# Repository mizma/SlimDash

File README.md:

# SlimDash

ErgoDash inspired low-profile key switch keyboard with embedded RP2040

## Features

* Ortho-Staggered Split keyboard layout
* Slim body (20-22mm depending on key caps and rubber feet used)
* Rigid body structure
* Per-Key RGB LED Matrix lighting
* USB-C connector
* Easy build utilizing PCBA service
  * Hand Soldering needed:
    * 70 x Kailh choc v1 hotswap sockets
    * 4 x tactile switches (2 x BOOT is optional)
    * 2 x trrs jack
    * 70 SK6812MINI-E (optional for RGB matrix)
  * Assembly
    * Just PH001 Philips screws necessary

### Variations

Currently there is only one variation.

* SlimDash rev.1
  * See the [readme](./hardware-rev1/README.md) in the hardware-rev1
    directory for build instructions.
  * For firmware, see the release section for pre-built firmware,
    or see [here](./firmware/keyboards/mzmkb/slimdash/) for the build source.
    * To build from source, follow the [instructions](https://docs.qmk.fm/newbs_getting_started)
      and copy the keyboard sources from this repo (until the keyboard
      is merged upstream) to build.

## Acknowlegements

* [ErgoDash by omkbd](https://github.com/omkbd/ErgoDash)
  * Inspiration for this keyboard
* [ergogen](https://github.com/ergogen/ergogen)
  * Tooling to assist in the key layout and mechanical design
* Tutorials to get me started with ergogen
  * [Let's Design A Keyboard With Ergogen v4](https://flatfootfox.com/ergogen-part2-outlines/)
  * [I Built My Dream Keyboard from Absolute Scratch](https://www.youtube.com/watch?v=7UXsD7nSfDY)
* Tools used for making `keyboard.json` _less_ tedious.
  * [KLE](https://www.keyboard-layout-editor.com/)
  * [Keyboard Firmware Builder](https://kbfirmware.com/)
  * [KBFirmware to qmk converter](https://noroadsleft.github.io/kbf_qmk_converter/)

## License

[SlimDash](https://github.com/mizma/SlimDash) by
[mizma](https://github.com/mizma) is licensed under
[Creative Commons Attribution-ShareAlike 4.0 International](https://creativecommons.org/licenses/by-sa/4.0/?ref=chooser-v1)
 -
 -

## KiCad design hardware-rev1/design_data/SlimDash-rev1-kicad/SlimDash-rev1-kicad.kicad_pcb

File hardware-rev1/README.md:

# hardware-rev1 Build Instructions

__IMPORTANT__.  Read through the entire instruction first before starting
the Assembly so you have a good idea on what to expect!

日本語の手順は[こちら](./README_ja.md)

## Parts List (for one keyboard)

* PCB
  * Order with PCBA using ./hardware-rev1/PCB/slimdash_v1.0.0.zip and
    BOM/CPL files in the same directory.
  * You will need 2 PCBs for one set of keyboard
  * Ordering Instructions below.
* Acrylic: Order cuts for following (number required for one keyboard)
  * `backplate_1left_3mm-157.1x131.2.zip` x 1
  * `backplate_1right_3mm-155.2x131.2.zip` x 1
  * `backplate_2both_2mm-157.1x131.2.zip` x 1
  * `backplate_2left_2mm-157.1x131.2.zip` x 1
  * `backplate_3both_2mm-157.1x39.02.zip` x 2
  * `baseplate_left_2mm-155.2x131.2.zip` x 1
  * `baseplate_right_2mm-155.2x131.2.zip` x 1
  * `coverplate_both_2mm-20.05x81.60.zip` x 2
  * Ordering Instructions below.
* Screws/standoff
  * 14x m2x4 through-hole standoff x 7 x 2 = 14
    * <https://www.monotaro.com/p/1111/2876/>
  * 6x m2x10 through-hole standoff x 3 x 2 = 6
    * <https://www.monotaro.com/p/1111/2998/>
  * 32x m2x4 screws x (10 + 6) x 2 = 32
    * <https://www.monotaro.com/p/2902/9395/>
  * 8x m2x6 screws x 4 x 2 = 8
    * <https://www.monotaro.com/p/2902/9413/>
* Hand-Soldered Items
  * 70x Kailh low profile (choc v1) switches of your choice
  * 70x Kailh low profile hotswap sockets
    * Can be ordered from LCSC with part number [C5333465](https://www.lcsc.com/product-detail/Mechanical-Keyboard-Shaft_Kailh-CPG135001S30_C5333465.html)
  * 4x 3x6x4.3 horizontal tact switch
    * <https://shop.yushakobo.jp/collections/all-keyboard-parts/products/a1600ed-01-1>
    * You can also order from LCSC with part number [C18078123](https://www.lcsc.com/product-detail/Tactile-Switches_Bossie-BX-TS-26-3643ZJ_C18078123.html)
    * MJTP1117/PHAP3363 from DigiKey should work as well [679-2400-ND](https://www.digikey.com/en/products/detail/apem-inc/MJTP1117/1795496)
    * [schematics](images/tactile-switch_3x6x4.3.jpg)
  * 2x TRRS socket (MJ-4PP-9) connector
    * <https://shop.yushakobo.jp/products/a0800tr-01-1>
  * (optional) 70x SK6812MINI-E
    * <https://shop.yushakobo.jp/products/sk6812mini-e-10?variant=40047782953121>
    * [C5149201](https://www.lcsc.com/product-detail/RGB-LEDs-Built-in-IC_OPSCO-Optoelectronics-SK6812MINI-E_C5149201.html)
* A Kailh Choc v1 compatible keycap set
  * recommend ortho linear keycap set (some examples below)
  * [MBK Legend Glow R2](https://fkcaps.com/keycaps/mbk/legend-glow)
  * [Chosfox CFX](https://chosfox.com/collections/keycaps)
* Other Accessories
  * 1x TRRS Cable (Straight)
    * <https://shop.yushakobo.jp/products/self-made-cable?variant=39623339737249>
    * Anything with Tip-Ring-Ring-Sleeve type 2.5mm jack with straight wiring
      should work.
  * 1x USB-C Cable (Type-A to C or Type-C to C depending on your host PC connector)
  * 8x Rubber feet stickers

### PCB Ordering Instructions (JLCPCB)

1. Go to [JLCPCB](https://jlcpcb.com/jp/)
2. In the "Upload Gerber File" select the `./PCB/slimdash_v1.0.0.zip` file.
3. In the order settings, select the following options.
    * Base Material: FR-4
    * Layers: 2
    * Dimensions: Automatically filled in. __DON'T TOUCH__
    * PCB order volume: your choice
    * Product type: Industrial/Consumer Electronics
    * Alternate Designs: 1
    * Panilization: No Panilization
    * PCB Thickness: 1.6mm
    * PCB Color: your choice
    * Silkscreen: your choice
    * Surface Finish: your choice (HASL is fine)
    * Copper Thickness: 1 oz
    * Via: Resist Cover
    * Minimum via diameter: Keep default
    * PCB dimension tolerance: Keep default
    * Check Manufacturing data: your choice
    * PCB marking: remove marking
    * Electrical Test: Keep default
    * Card Edge connector: No
    * Castelated through-hole: No
    * Edge Plating: No
4. Select PCB Assembly option
    * PCBA Type: Economic
    * Assembly side: Top side
    * PCBA volume: same as PCB order volume (unless you are going to
      hand-solder SMT packages)
    * Tooling Hole: Added by Customer
    * Part Placement check: Yes
    * Part Selection: By Customer
    * Other Detail options: your choice.  Read JLCPCB descriptions carefully.
5. Go to next and Upload the [BOM](./PCB/bom.csv) file and [CPL](./PCB/CPL.csv) file
6. Check that the layout of the PCB has no errors. (It should look like the following)
    * 
7. Go to Quote and Order.

### Acrylic Ordering Instructions

1. Go to [Elecrow](https://www.elecrow.com/acrylic-cutting.html)
2. Upload each zip files in the Acrylic folder to order
    * Dimensions and Thickness should match the dimensions in the .zip file name.
      * i.e. for backplate_1left_3mm-157.1x131.2.zip, width x heigh should be 157.1x131.2
        and thickness of 3mm
    * Qty can be any number you require.
    * Color can be anything, but 2mm thickness only support Transparent, black or white.

## Assembly Instructions

First, solder the 90 degree tactile switch to the RST and BOOT.

The switch should be implemented on the top side for each hand.
Picture above shows the left hand side implementation.

Tact switch should be soldered before the TRRS jack.  TRRS jack
is then soldered on the same side of the board as the tactile
switches.

Once both the Tactile switches and the TRRS jack is implemented,
it should look like the following for left and right hand side.

After the TRRS and Tactile switches, apply pre-solder to one side of
the pad of each choc v1 hotswap sockets as shown below.

This pre-solder must be done on the opposite side from the tactile switches and
TRRS jacks.

After pre-solder is applied, place the hotswap sockets in place, and
use the soldering iron to pre-fuse the socket onto the pad.

Once the sockets are held in place, apply solder to the other side for
proper soldering, and then apply extra solder on the pre-fused side to
secure the socket in place.

When applying solder to the socket, make sure you do not over-apply solder.
If the solder bulges beyond the pad area (surpassing the yellow line in Picture
below), the acrylic will interfere and will not assemble properly.

If the solder interferes with the acrylic, don't force the assembly and remove
some solder using solder wick.

__OPTIONAL__: you may solder the SK6812MINI-E RGB LEDs at this point if you would
like.  See section below for extra instructions.

After Sockets are soldered, place the baseplate on the front side and insert
the kailh choc v1 keyswitches of your choice.  After all the switches are inserted,
place the 4mm long M2 spacer (standoff) from the back side, and loosely secure it
with the 4mm long M2 screws.

Flip the board to the back, place the backplate 1 ~ 3 and screw in the
4mm and 6mm screws. 6mm screws are used for the screw holes that go
through backplate 3.

After backplate is assembled, place the 10mm M2 spacer in the MCU areas
3 holes, and secure them with M2 screws, placing the coverplate on the top.
Put your choice of key caps.

You may apply rubber feet stickers on the back side for better stability and
stop the keyboard from sliding around in use.

### RGB Instructions

You will need to first jump the `JP1` solder jumper right next to the TRRS Jack.

Then solder the SK6812MINI-E from the back of the PCB, with the light emitting
side facing up.

See the pictures for the correct orientation (PIN1 is marked with yellow dot).

Note: the pin that has a diagonal cut is NOT PIN1.  Diagonal cut pin is diagonally
opposite from PIN1 marked on the picture above with yellow dot.

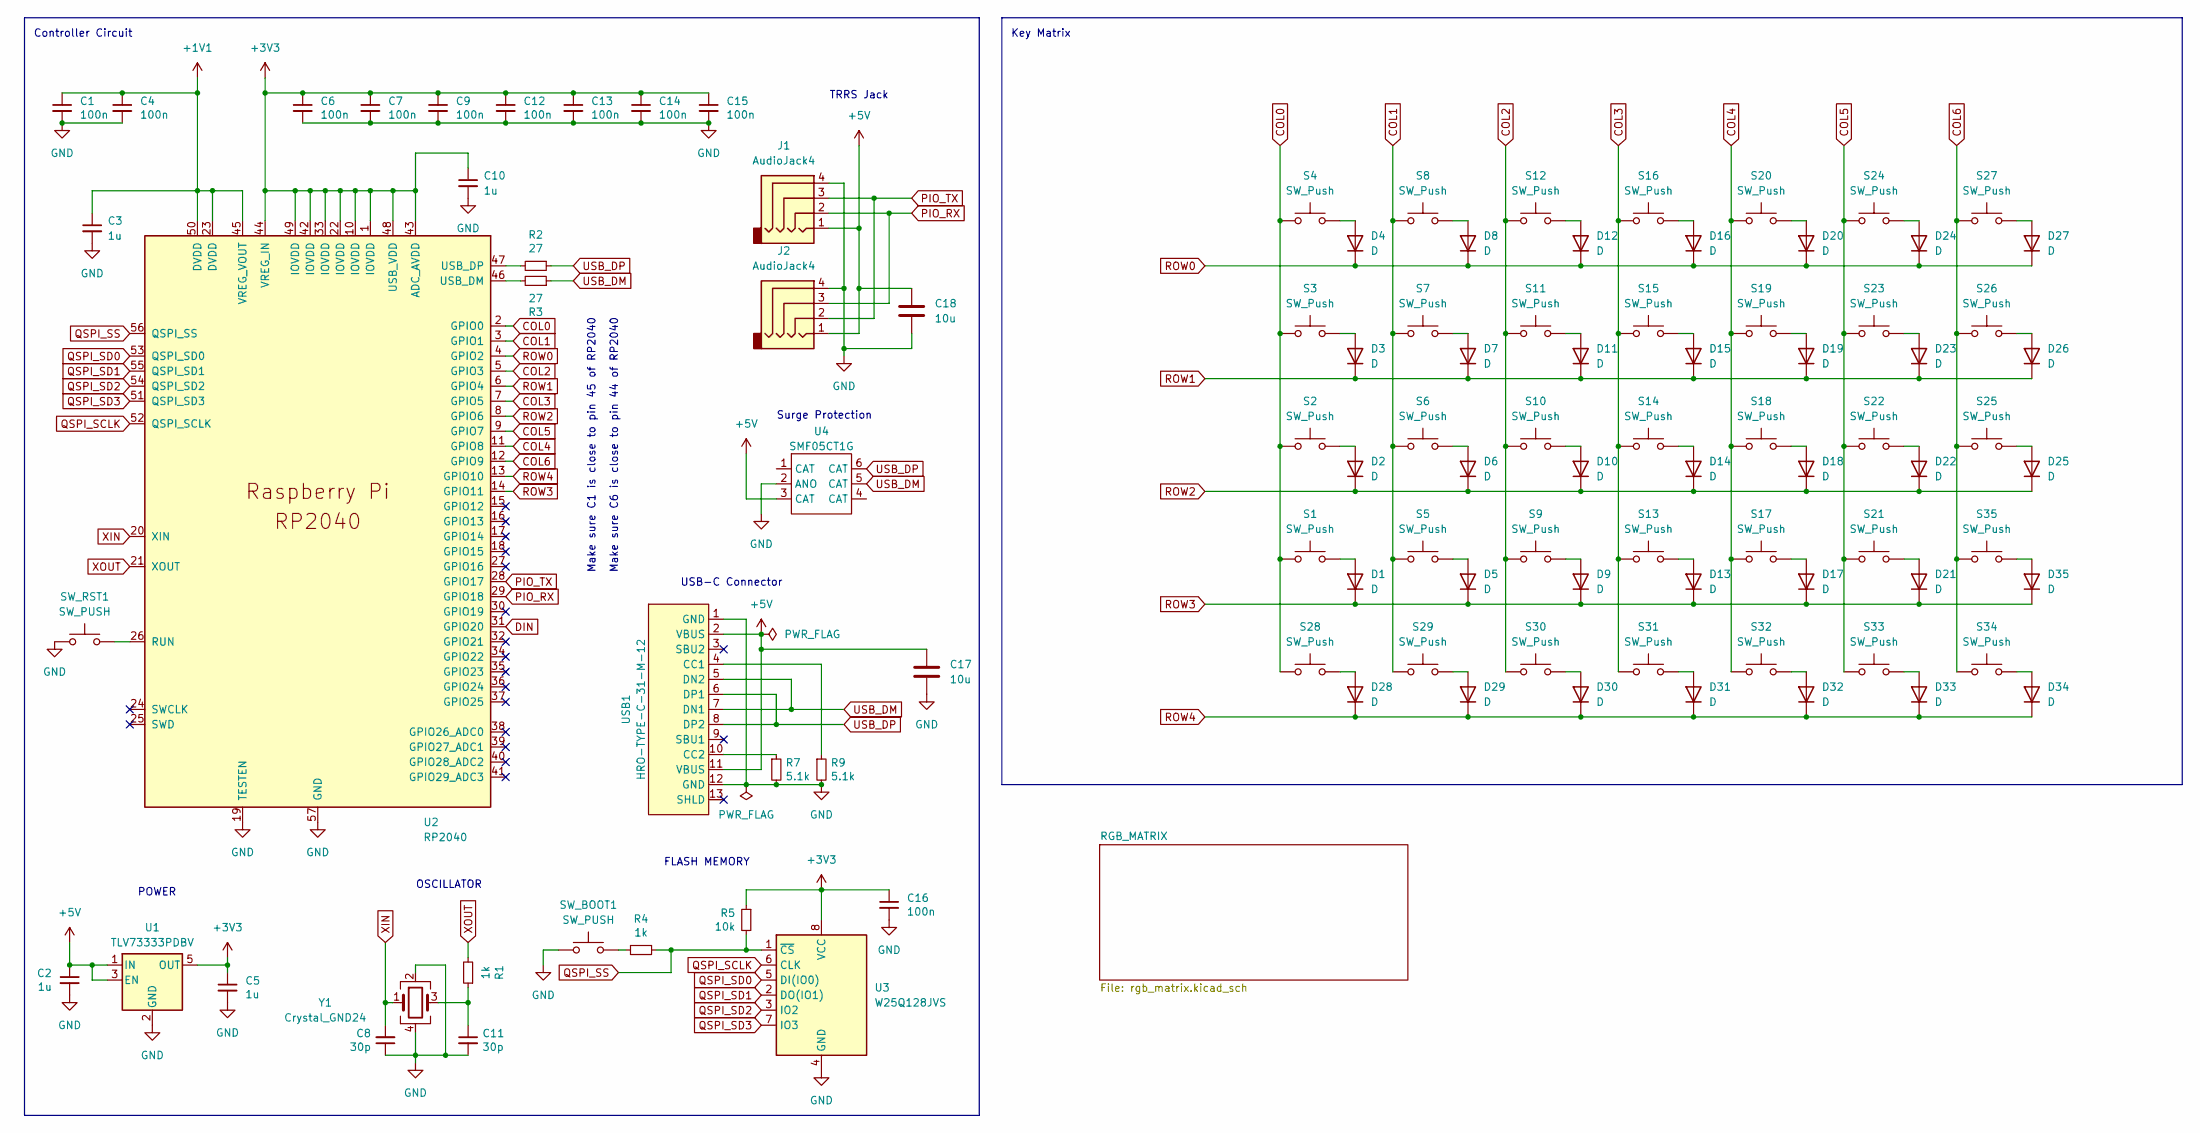
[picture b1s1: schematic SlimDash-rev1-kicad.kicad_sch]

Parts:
C1, C4, C6, C7, C9, C12, C13, C14, C15, C16: 100n; C_0402_1005Metric; LCSC C1525
C2, C3, C5, C10: 1u; C_0402_1005Metric; LCSC C52923
C8, C11: 30p; C_0402_1005Metric; LCSC C1570
C17, C18: 10u; C_0402_1005Metric; LCSC C315248
D1, D2, D3, D4, D5, D6, D7, D8, D9, D10, D11, D12, D13, D14, D15, D16, D17, D18, D19, D20, D21, D22, D23, D24, D25, D26, D27, D28, D29, D30, D31, D32, D33, D34, D35: D; D_SOD-123F; LCSC C2908120
J1, J2: AudioJack4; TRRS_jack
R1, R4: 1k; R_0402_1005Metric; LCSC C11702
R2, R3: 27; R_0402_1005Metric; LCSC C138021
R5: 10k; R_0402_1005Metric; LCSC C25744
R7, R9: 5.1k; R_0402_1005Metric; LCSC C25905
S1, S2, S3, S4, S5, S6, S7, S8, S9, S10, S11, S12, S13, S14, S15, S16, S17, S18, S19, S20, S21, S22, S23, S24, S25, S26, S27, S28, S29, S30, S31, S32, S33, S34, S35: SW_Push; Kailh_socket_PG1350_reversible
SW_BOOT1: SW_PUSH; SW_Tactile_Yushakobo 3x6x4.3mm
SW_RST1: SW_PUSH; SW_Tactile_Yushakobo 3x6x4.3mm
U1: TLV73333PDBV; SOT-23-5; LCSC C134139
U2: RP2040; RP2040-QFN-56; LCSC C2040
U3: W25Q128JVS; SOIC-8_5.23x5.23mm_P1.27mm; LCSC C97521
U4: SMF05CT1G; SOT-363_SC-70-6; LCSC C15879
USB1: HRO-TYPE-C-31-M-12; USB-C_SMD-TYPE-C-31-M-12; LCSC C165948
Y1: Crystal_GND24; Crystal_SMD_3225-4Pin_3.2x2.5mm; LCSC C9002

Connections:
+1V1: C1.1, C3.1, C4.1, U2.23 (DVDD), U2.45 (VREG_VOUT), U2.50 (DVDD)
+3V3: C5.1, C6.1, C7.1, C9.1, C10.1, C12.1, C13.1, C14.1, C15.1, C16.1, R5.1, U1.5 (OUT), U2.1 (IOVDD), U2.10 (IOVDD), U2.22 (IOVDD), U2.33 (IOVDD), U2.42 (IOVDD), U2.43 (ADC_AVDD), U2.44 (VREG_IN), U2.48 (USB_VDD), U2.49 (IOVDD), U3.8 (VCC); also elsewhere on the board
+5V: C2.1, C17.1, C18.1, J1.1, J2.1, U1.1 (IN), U1.3 (EN), U4.3 (CAT), USB1.2 (VBUS), USB1.11 (VBUS); also elsewhere on the board
COL0: S1.1, S2.1, S3.1, S4.1, S28.1, U2.2 (GPIO0)
COL1: S5.1, S6.1, S7.1, S8.1, S29.1, U2.3 (GPIO1)
COL2: S9.1, S10.1, S11.1, S12.1, S30.1, U2.5 (GPIO3)
COL3: S13.1, S14.1, S15.1, S16.1, S31.1, U2.7 (GPIO5)
COL4: S17.1, S18.1, S19.1, S20.1, S32.1, U2.11 (GPIO8)
COL5: S21.1, S22.1, S23.1, S24.1, S33.1, U2.9 (GPIO7)
COL6: S25.1, S26.1, S27.1, S34.1, S35.1, U2.12 (GPIO9)
DIN: U2.31 (GPIO20); also elsewhere on the board
GND: C1.2, C2.2, C3.2, C4.2, C5.2, C6.2, C7.2, C8.1, C9.2, C10.2, C11.2, C12.2, C13.2, C14.2, C15.2, C16.2, C17.2, C18.2, J1.4, J2.4, R7.2, R9.2, SW_BOOT1.1, SW_RST1.1, U1.2 (GND), U2.19 (TESTEN), U2.57 (GND), U3.4 (GND), U4.2 (ANO), USB1.1 (GND), USB1.12 (GND), Y1.2, Y1.4; also elsewhere on the board
unnamed: C11.1, R1.1, Y1.3
unnamed: D1.2 (A), S1.2
unnamed: D2.2 (A), S2.2
unnamed: D3.2 (A), S3.2
unnamed: D4.2 (A), S4.2
unnamed: D5.2 (A), S5.2
unnamed: D6.2 (A), S6.2
unnamed: D7.2 (A), S7.2
unnamed: D8.2 (A), S8.2
unnamed: D9.2 (A), S9.2
unnamed: D10.2 (A), S10.2
unnamed: D11.2 (A), S11.2
unnamed: D12.2 (A), S12.2
unnamed: D13.2 (A), S13.2
unnamed: D14.2 (A), S14.2
unnamed: D15.2 (A), S15.2
unnamed: D16.2 (A), S16.2
unnamed: D17.2 (A), S17.2
unnamed: D18.2 (A), S18.2
unnamed: D19.2 (A), S19.2
unnamed: D20.2 (A), S20.2
unnamed: D21.2 (A), S21.2
unnamed: D22.2 (A), S22.2
unnamed: D23.2 (A), S23.2
unnamed: D24.2 (A), S24.2
unnamed: D25.2 (A), S25.2
unnamed: D26.2 (A), S26.2
unnamed: D27.2 (A), S27.2
unnamed: D28.2 (A), S28.2
unnamed: D29.2 (A), S29.2
unnamed: D30.2 (A), S30.2
unnamed: D31.2 (A), S31.2
unnamed: D32.2 (A), S32.2
unnamed: D33.2 (A), S33.2
unnamed: D34.2 (A), S34.2
unnamed: D35.2 (A), S35.2
unnamed: R4.2, SW_BOOT1.2
unnamed: SW_RST1.2, U2.26 (RUN)
unnamed: R3.2, U2.46 (USB_DM)
unnamed: R2.2, U2.47 (USB_DP)
unnamed: R9.1, USB1.4 (CC1)
unnamed: R7.1, USB1.10 (CC2)
PIO_RX: J1.2, J2.3, U2.29 (GPIO18)
PIO_TX: J1.3, J2.2, U2.28 (GPIO17)
QSPI_SCLK: U2.52 (QSPI_SCLK), U3.6 (CLK)
QSPI_SD0: U2.53 (QSPI_SD0), U3.5 (DI(IO0))
QSPI_SD1: U2.55 (QSPI_SD1), U3.2 (DO(IO1))
QSPI_SD2: U2.54 (QSPI_SD2), U3.3 (IO2)
QSPI_SD3: U2.51 (QSPI_SD3), U3.7 (IO3)
QSPI_SS: R4.1, R5.2, U2.56 (QSPI_SS), U3.1 (~CS)
ROW0: D4.1 (K), D8.1 (K), D12.1 (K), D16.1 (K), D20.1 (K), D24.1 (K), D27.1 (K), U2.4 (GPIO2)
ROW1: D3.1 (K), D7.1 (K), D11.1 (K), D15.1 (K), D19.1 (K), D23.1 (K), D26.1 (K), U2.6 (GPIO4)
ROW2: D2.1 (K), D6.1 (K), D10.1 (K), D14.1 (K), D18.1 (K), D22.1 (K), D25.1 (K), U2.8 (GPIO6)
ROW3: D1.1 (K), D5.1 (K), D9.1 (K), D13.1 (K), D17.1 (K), D21.1 (K), D35.1 (K), U2.14 (GPIO11)
ROW4: D28.1 (K), D29.1 (K), D30.1 (K), D31.1 (K), D32.1 (K), D33.1 (K), D34.1 (K), U2.13 (GPIO10)
USB_DM: R3.1, U4.5 (CAT), USB1.5 (DN2), USB1.7 (DN1)
USB_DP: R2.1, U4.6 (CAT), USB1.6 (DP1), USB1.8 (DP2)
XIN: C8.2, U2.20 (XIN), Y1.1
XOUT: R1.2, U2.21 (XOUT)

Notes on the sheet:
Surge Protection
Controller Circuit
FLASH MEMORY
Make sure C1 is close to pin 45 of RP2040
USB-C Connector
OSCILLATOR
Key Matrix
TRRS Jack
Make sure C6 is close to pin 44 of RP2040
POWER

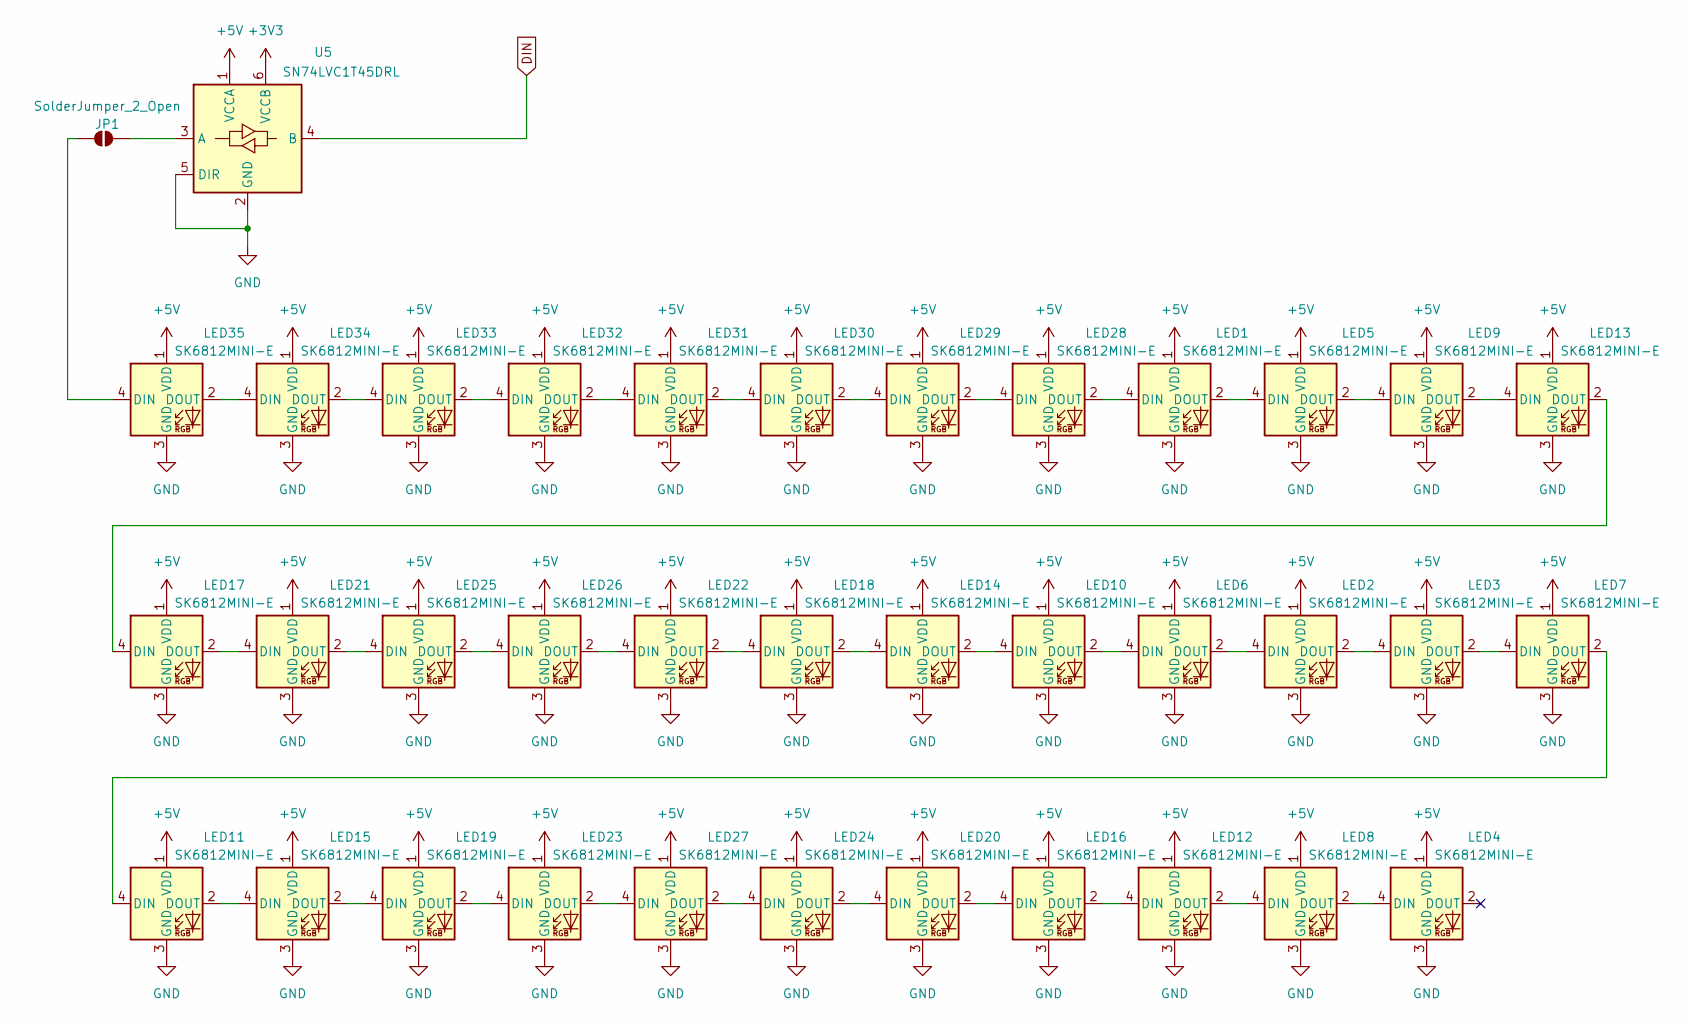
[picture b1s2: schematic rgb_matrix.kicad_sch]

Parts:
JP1: SolderJumper_2_Open; SolderJumper-2_P1.3mm_Open_RoundedPad1.0x1.5mm
LED1, LED2, LED3, LED4, LED5, LED6, LED7, LED8, LED9, LED10, LED11, LED12, LED13, LED14, LED15, LED16, LED17, LED18, LED19, LED20, LED21, LED22, LED23, LED24, LED25, LED26, LED27, LED28, LED29, LED30, LED31, LED32, LED33, LED34, LED35: SK6812MINI-E; SK6812-MINI-E_Reversible; LCSC C5149201
U5: SN74LVC1T45DRL; SOT-563_SN74LVC1T45DRLR; LCSC C352970

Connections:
+3V3: U5.6 (VCCB); also elsewhere on the board
+5V: LED1.1 (VDD), LED2.1 (VDD), LED3.1 (VDD), LED4.1 (VDD), LED5.1 (VDD), LED6.1 (VDD), LED7.1 (VDD), LED8.1 (VDD), LED9.1 (VDD), LED10.1 (VDD), LED11.1 (VDD), LED12.1 (VDD), LED13.1 (VDD), LED14.1 (VDD), LED15.1 (VDD), LED16.1 (VDD), LED17.1 (VDD), LED18.1 (VDD), LED19.1 (VDD), LED20.1 (VDD), LED21.1 (VDD), LED22.1 (VDD), LED23.1 (VDD), LED24.1 (VDD), LED25.1 (VDD), LED26.1 (VDD), LED27.1 (VDD), LED28.1 (VDD), LED29.1 (VDD), LED30.1 (VDD), LED31.1 (VDD), LED32.1 (VDD), LED33.1 (VDD), LED34.1 (VDD), LED35.1 (VDD), U5.1 (VCCA); also elsewhere on the board
DIN: U5.4 (B); also elsewhere on the board
GND: LED1.3 (GND), LED2.3 (GND), LED3.3 (GND), LED4.3 (GND), LED5.3 (GND), LED6.3 (GND), LED7.3 (GND), LED8.3 (GND), LED9.3 (GND), LED10.3 (GND), LED11.3 (GND), LED12.3 (GND), LED13.3 (GND), LED14.3 (GND), LED15.3 (GND), LED16.3 (GND), LED17.3 (GND), LED18.3 (GND), LED19.3 (GND), LED20.3 (GND), LED21.3 (GND), LED22.3 (GND), LED23.3 (GND), LED24.3 (GND), LED25.3 (GND), LED26.3 (GND), LED27.3 (GND), LED28.3 (GND), LED29.3 (GND), LED30.3 (GND), LED31.3 (GND), LED32.3 (GND), LED33.3 (GND), LED34.3 (GND), LED35.3 (GND), U5.2 (GND), U5.5 (DIR); also elsewhere on the board
unnamed: JP1.1 (A), U5.3 (A)
unnamed: JP1.2 (B), LED35.4 (DIN)
unnamed: LED1.4 (DIN), LED28.2 (DOUT)
unnamed: LED1.2 (DOUT), LED5.4 (DIN)
unnamed: LED2.4 (DIN), LED6.2 (DOUT)
unnamed: LED2.2 (DOUT), LED3.4 (DIN)
unnamed: LED3.2 (DOUT), LED7.4 (DIN)
unnamed: LED4.4 (DIN), LED8.2 (DOUT)
unnamed: LED5.2 (DOUT), LED9.4 (DIN)
unnamed: LED10.4 (DIN), LED14.2 (DOUT)
unnamed: LED6.4 (DIN), LED10.2 (DOUT)
unnamed: LED7.2 (DOUT), LED11.4 (DIN)
unnamed: LED11.2 (DOUT), LED15.4 (DIN)
unnamed: LED12.4 (DIN), LED16.2 (DOUT)
unnamed: LED8.4 (DIN), LED12.2 (DOUT)
unnamed: LED9.2 (DOUT), LED13.4 (DIN)
unnamed: LED13.2 (DOUT), LED17.4 (DIN)
unnamed: LED14.4 (DIN), LED18.2 (DOUT)
unnamed: LED15.2 (DOUT), LED19.4 (DIN)
unnamed: LED16.4 (DIN), LED20.2 (DOUT)
unnamed: LED17.2 (DOUT), LED21.4 (DIN)
unnamed: LED18.4 (DIN), LED22.2 (DOUT)
unnamed: LED19.2 (DOUT), LED23.4 (DIN)
unnamed: LED20.4 (DIN), LED24.2 (DOUT)
unnamed: LED21.2 (DOUT), LED25.4 (DIN)
unnamed: LED22.4 (DIN), LED26.2 (DOUT)
unnamed: LED23.2 (DOUT), LED27.4 (DIN)
unnamed: LED24.4 (DIN), LED27.2 (DOUT)
unnamed: LED25.2 (DOUT), LED26.4 (DIN)
unnamed: LED28.4 (DIN), LED29.2 (DOUT)
unnamed: LED29.4 (DIN), LED30.2 (DOUT)
unnamed: LED30.4 (DIN), LED31.2 (DOUT)
unnamed: LED31.4 (DIN), LED32.2 (DOUT)
unnamed: LED32.4 (DIN), LED33.2 (DOUT)
unnamed: LED33.4 (DIN), LED34.2 (DOUT)
unnamed: LED34.4 (DIN), LED35.2 (DOUT)

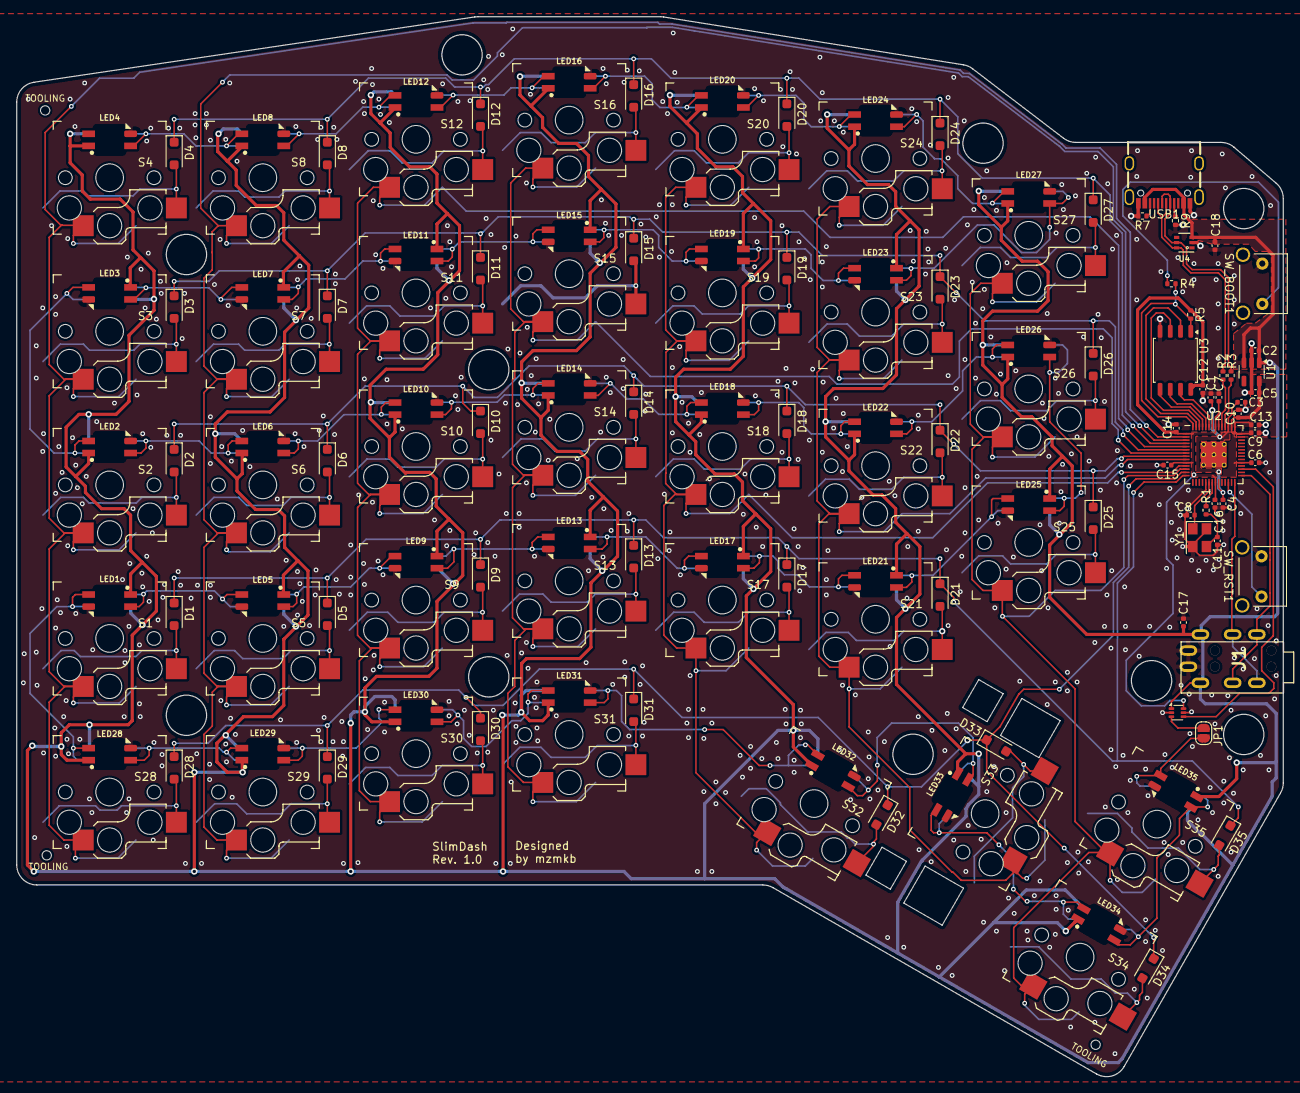
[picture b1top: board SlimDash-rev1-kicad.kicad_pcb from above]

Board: 2 copper layers, 157.1 x 131.5 mm, 146 parts (1 on the bottom side), 107 nets.

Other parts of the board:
Kailh PG1350_2U Stabilizer: Choc; Kailh-PG1350-2u-stabilizer
TOOLING: JLCPCB_Tooling
TOOLING#2, TOOLING#3: JLCPCB_Tooling

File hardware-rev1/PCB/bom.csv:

Designator,Footprint,Quantity,Value,LCSC Part #
"C1, C12, C13, C14, C15, C16, C4, C6, C7, C9",0402,10,100n,C1525
"C10, C2, C3, C5",0402,4,1u,C52923
"C11, C8",0402,2,30p,C1570
"C17, C18",0402,2,10u,C315248
"D1, D10, D11, D12, D13, D14, D15, D16, D17, D18, D19, D2, D20, D21, D22, D23, D24, D25, D26, D27, D28, D29, D3, D30, D31, D32, D33, D34, D35, D4, D5, D6, D7, D8, D9",D_SOD-123F,35,D,C2908120
"LED1, LED10, LED11, LED12, LED13, LED14, LED15, LED16, LED17, LED18, LED19, LED2, LED20, LED21, LED22, LED23, LED24, LED25, LED26, LED27, LED28, LED29, LED3, LED30, LED31, LED32, LED33, LED34, LED35, LED4, LED5, LED6, LED7, LED8, LED9",SK6812-MINI-E_Reversible,35,SK6812MINI-E,C5149201
"R1, R4",0402,2,1k,C11702
"R2, R3",0402,2,27,C138021
R5,0402,1,10k,C25744
"R7, R9",0402,2,5.1k,C25905
"S1, S10, S11, S12, S13, S14, S15, S16, S17, S18, S19, S2, S20, S21, S22, S23, S24, S25, S26, S27, S28, S29, S3, S30, S31, S32, S33, S34, S35, S4, S5, S6, S7, S8, S9",Kailh_socket_PG1350_reversible,35,SW_Push,
U1,SOT-23-5,1,TLV73333PDBV,C134139
U2,RP2040-QFN-56,1,RP2040,C2040
U3,SOIC-8_5.23x5.23mm_P1.27mm,1,W25Q128JVS,C97521
U4,SOT-363_SC-70-6,1,SMF05CT1G,C15879
U5,SOT-563_SN74LVC1T45DRLR,1,SN74LVC1T45DRL,C352970
USB1,USB-C_SMD-TYPE-C-31-M-12,1,HRO-TYPE-C-31-M-12,C165948
Y1,Crystal_SMD_3225-4Pin_3.2x2.5mm,1,Crystal_GND24,C9002

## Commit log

2024-05-05 add submodules for kicad library
2024-05-10 add externals
2024-12-04 add initial ergogen config
2024-12-04 make initial left boards
2024-12-04 base board set complete
2024-12-04 add TODOs in README
2024-12-04 add more TODO
2024-12-05 initial import of ergogen pcb to kicad proj
2024-12-05 add memo
2024-12-05 add more memo
2024-12-06 fix some positioning and net labels
2024-12-06 start planning for routing
2024-12-07 add more components to design data
2024-12-07 fix outline where cutouts were too close
2024-12-07 add surge protection
2024-12-07 trace routing progress
2024-12-08 more routing and fixing footprints
2024-12-08 compensate for trrs jack change
2024-12-08 update submodule
2024-12-08 wire updates on rgb leds
2024-12-09 fix backplate conflict with JP1
2024-12-09 update TODOs
2024-12-09 fix image size
2024-12-09 fix ergogen artefact
2024-12-15 finalize pcb layout
2024-12-15 add logo to pcb
2024-12-15 add manufacturing files
2024-12-15 add logo in README
2024-12-31 update acrylic design data
2024-12-31 rename to show board size
2024-12-31 add part list
2024-12-31 add images for PCB
2025-01-02 add firmware files
2025-01-02 add vialrgb support
2025-01-05 add right hand matrix
2025-01-06 add KC_GRV to RAISE layer
2025-01-06 match default keymap on vial
2025-01-06 add UID
2025-01-07 fix license
2025-01-07 fix layout offset
2025-01-07 run qmk format-json
2025-01-08 shift layout to remove x offset
2025-01-09 add image
2025-01-09 add image and missing CAPS key mapping
2025-01-09 Add Assembly instructions
2025-01-09 fix typo
2025-01-09 add schematic
2025-01-09 add rubber feet pics
2025-01-09 add caution
2025-01-09 add PCB image
2025-01-09 sync with qmk_firmware PR
2025-01-09 match vial default keymap to default
2025-01-09 reformat vial.json
2025-01-09 add more info on firmware
2025-01-10 add upstream review changes
2025-01-10 match vial to qmk_firmware default map
2025-01-10 add Japanese README
2025-01-10 update to match changes in qmk_firmware repo
2025-01-27 add submodule reset script
2025-05-04 update firmware with latest merged mzmkb
2025-05-04 fix keymap for vial RGB backlight control
2025-05-04 Update README.md
    Remove TODOs
